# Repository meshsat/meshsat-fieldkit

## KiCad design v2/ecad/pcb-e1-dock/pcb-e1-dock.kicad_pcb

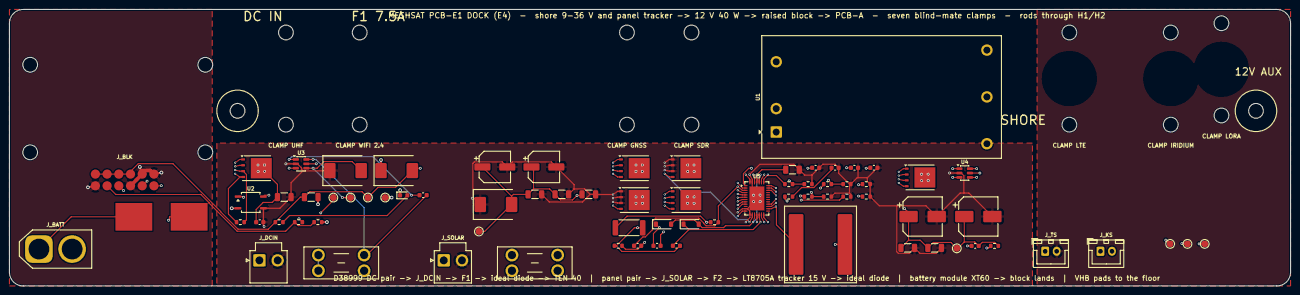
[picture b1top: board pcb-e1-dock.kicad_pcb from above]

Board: 4 copper layers, 278.0 x 60.0 mm, 97 parts (0 on the bottom side), 44 nets.

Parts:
C1, C13, C14: 10u 50V; C_1206_3216Metric
C2, C23: 100n; C_0603_1608Metric
C3: 22u 25V; C_1206_3216Metric
C4, C28: 100n 50V; C_0603_1608Metric
C11, C12: 100u 35V Panasonic EEHZK1V101XP hybrid polymer (7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; CP_Elec_6.3x7.7
C15: 4.7u 50V; C_1206_3216Metric
C16: 1n; C_0603_1608Metric
C17, C18: 470n 25V; C_0603_1608Metric
C19: 4.7u 25V; C_1206_3216Metric
C20: 1u; C_0603_1608Metric
C21: 4.7n; C_0603_1608Metric
C22: 100p; C_0603_1608Metric
C24, C25: 39u 35V Panasonic 35SVPF39M polymer (6.9 mm); CP_Elec_8x6.7
C26, C27: 10u 25V; C_1206_3216Metric
D1: SMCJ33A (input surge, datasheet 50 V 100 ms); D_SMC
D3: SMCJ15A; D_SMC
D4: SMCJ33A (panel surge); D_SMC
D5: BAT54 boost diode INTVCC -> BOOST1; D_SOD-123
D6: BAT54 boost diode INTVCC -> BOOST2; D_SOD-123
F1: 7.5 A mini blade (Keystone 3568 holder, in the cl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; Fuseholder_Blade_Mini_Keystone_3568
F2: 10 A mini blade (Keystone 3568 holder, in the cle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; Fuseholder_Blade_Mini_Keystone_3568
H1, H2: M3 rod pass-through, PCB-A standoff stands here; MountingHole_3.2mm_M3
H3, H4, H5, H6: M3 standoff, raised block; MountingHole_3.2mm_M3
H7, H8: M3, float clamp UHF; MountingHole_3.2mm_M3
H9, H10: M3, float clamp WIFI 2.4; MountingHole_3.2mm_M3
H11, H12: M3, float clamp GNSS; MountingHole_3.2mm_M3
H13, H14: M3, float clamp SDR; MountingHole_3.2mm_M3
H15, H16: M3, float clamp LTE; MountingHole_3.2mm_M3
H17, H18: M3, float clamp IRIDIUM; MountingHole_3.2mm_M3
H19, H20: M3, float clamp LORA; MountingHole_3.2mm_M3
J_BATT: battery module lead (XT60-M, 60 A): + - ; fused 4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; AMASS_XT60-M_1x02_P7.20mm_Vertical
J_BLK: solder lands for the 12 signal wires to the block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; PogoTargets_2x6
J_DCIN: shore DC in 9-36 V, lead from the D38999/20FC4PN 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; JST_VH_B2P-VH_1x02_P3.96mm_Vertical
J_KS: Kelvin sense lead from the module positive termin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; JST_XH_B2B-XH-A_1x02_P2.50mm_Vertical
J_SOLAR: bare 12 V class panel in, lead from the D38999 sp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; JST_VH_B2P-VH_1x02_P3.96mm_Vertical
J_TS: module thermistor lead (XH2.5): 103AT to the char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; JST_XH_B2B-XH-A_1x02_P2.50mm_Vertical
L1: 10uH Coilcraft XAL1510-103MED (Isat 26 A, 10.0 mm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; L_Coilcraft_XAL1510-103
LED1: green: shore 12 V present; LED_0603_1608Metric
P_CN: solder pad, 12 AWG wire to the block board return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; SolderPad_8x6
P_CP: solder pad, 12 AWG wire to the block board CELL+ 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; SolderPad_8x6
Q1, Q2: BSC039N06NS 60 V 3.9 mOhm N-FET (PG-TDSON-8: 1-3 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; TDSON-8-1
Q3: BSC028N06NS 60 V 2.8 mOhm N-FET, M1 buck top (TDS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; TDSON-8-1
Q4: BSC039N06NS 60 V N-FET, M2 buck bottom; TDSON-8-1
Q5: BSC028N06NS 60 V N-FET, M3 boost bottom; TDSON-8-1
Q6: BSC039N06NS 60 V N-FET, M4 boost top; TDSON-8-1
R1, R4, R18: 100k; R_0603_1608Metric
R2: 2.2k; R_0603_1608Metric
R3: 330R; R_0603_1608Metric
R5: 5 mOhm 1% 3 W 2512 RSENSE (RALEC LR2512-23R005F4); R_2512_6332Metric
R6, R7: 100R; R_0603_1608Metric
R8: 102k 1% (RFBIN1: panel point 17.6 V); R_0603_1608Metric
R9: 7.50k 1% (RFBIN2); R_0603_1608Metric
R10: 115k 1% (RFBOUT1: 15.1 V); R_0603_1608Metric
R11: 10.0k 1% (RFBOUT2); R_0603_1608Metric
R12: 215k 1% (RT: 202 kHz); R_0603_1608Metric
R13, R16, R17: 10k; R_0603_1608Metric
R14: 100k 1%; R_0603_1608Metric
R15: 15.0k 1% (SHDN: enable above about 9.5 V); R_0603_1608Metric
TP1: DC_IN; TestPoint_Pad_D1.5mm
TP2: DC_P; TestPoint_Pad_D1.5mm
TP3: SHORE_12V; TestPoint_Pad_D1.5mm
TP4: GND; TestPoint_Pad_D1.5mm
TP5: PV_P; TestPoint_Pad_D1.5mm
TP6: TRK_OUT; TestPoint_Pad_D1.5mm
TP7: BLK_SPARE; TestPoint_Pad_D1.5mm
TP8: CELL_P_MOD; TestPoint_Pad_D1.5mm
TP9: CELL_N_MOD; TestPoint_Pad_D1.5mm
U1: TRACO TEN 40-2412WIN: isolated 9-36 V in, 12 V 3.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; Converter_DCDC_TRACO_TEN40-110xxWIRH_THT
U2: EL817S / PC817 optocoupler: LED from PCB-A SHORE_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; SOP-4_3.8x4.1mm_P2.54mm
U3, U4: LM74700-Q1 ideal-diode controller: 1 VCAP 2 GND 3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; SOT-23-6
U5: LT8705A buck-boost controller, 38-lead QFN 5x7 (p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; WQFN-38-1EP_5x7mm_P0.5mm_EP3.15x5.15mm

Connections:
/BLK_SPARE: J_BLK.12, TP7.1
/CELL_N_MOD: J_BATT.2, P_CN.1, TP9.1
/CELL_P_MOD: J_BATT.1, P_CP.1, TP8.1
/CELL_SENSE_P: J_BLK.11, J_KS.1
/DC_F: C4.2, F1.2, Q1.1, Q1.2, Q1.3, R1.2, U3.3, U3.6
/DC_IN: F1.1, J_DCIN.1, TP1.1
/DC_N: C1.2, C2.2, C11.2, C12.2, C13.2, C14.2, C15.2, C19.2, C20.2, C21.2, C22.2, C23.2, C24.2, C25.2, C26.2, C27.2, D1.1, D4.1, J_DCIN.2, J_SOLAR.2, Q4.1, Q4.2, Q4.3, Q5.1, Q5.2, Q5.3, R9.2, R11.2, R12.2, R15.2, R16.2, R17.2, U1.2, U2.3, U3.2, U4.2, U5.11, U5.13, U5.37, U5.39
/DC_P: C1.1, C2.1, D1.2, Q1.5, Q2.5, TP2.1, U1.1, U3.4, U4.4
/LED_A: LED1.2, R2.2
/OPTO_A: R3.2, U2.1
/PV_IN: F2.1, J_SOLAR.1
/PV_P: C11.1, C12.1, C13.1, C14.1, C15.1, D4.2, F2.2, Q3.5, R8.1, R14.1, TP5.1, U5.32, U5.33, U5.34
/Q1_G: Q1.4, R1.1, U3.5
/Q2_G: Q2.4, R18.1, U4.5
/REMOTE: U1.3, U2.4
/SHORE_12V: C3.1, D3.2, J_BLK.1, J_BLK.2, J_BLK.3, J_BLK.4, R2.1, TP3.1, U1.4
/SHORE_INHIBIT: J_BLK.8, R3.1, R4.1
/TRK_BG1: Q4.4, U5.14
/TRK_BG2: Q5.4, U5.16
/TRK_BOOST1: C17.1, D5.1, U5.23
/TRK_BOOST2: C18.1, D6.1, U5.17
/TRK_CSN: C16.2, R7.2, U5.2
/TRK_CSP: C16.1, R6.2, U5.3
/TRK_FBIN: R8.2, R9.1, U5.5
/TRK_FBOUT: R10.2, R11.1, U5.6
/TRK_IMONI: R16.1, U5.38
/TRK_IMONO: R17.1, U5.7
/TRK_INTVCC: C19.1, D5.2, D6.2, U5.15, U5.35, U5.36
/TRK_LDO33: C20.1, U5.4
/TRK_LSENSE: L1.2, R5.1, R6.1
/TRK_OUT: C24.1, C25.1, C26.1, C27.1, C28.2, Q2.1, Q2.2, Q2.3, Q6.5, R10.1, R18.2, TP6.1, U4.3, U4.6, U5.29, U5.30, U5.31
/TRK_RT: R12.1, U5.12
/TRK_SHDN: R14.2, R15.1, U5.1
/TRK_SS: C23.1, U5.9
/TRK_SW1: C17.2, L1.1, Q3.1, Q3.2, Q3.3, Q4.5, U5.21
/TRK_SW2: C18.2, Q5.5, Q6.1, Q6.2, Q6.3, R5.2, R7.1, U5.19
/TRK_TG1: Q3.4, U5.22
/TRK_TG2: Q6.4, U5.18
/TRK_VC: C22.1, R13.1, U5.8
/TRK_VCC1: C21.1, R13.2
/TS_MOD: J_BLK.9, J_TS.1
/U3_VCAP: C4.1, U3.1
/U4_VCAP: C28.1, U4.1
GND: C3.2, D3.1, J_BLK.5, J_BLK.6, J_BLK.7, J_BLK.10, J_TS.2, LED1.1, R4.2, TP4.1, U1.5, U2.2

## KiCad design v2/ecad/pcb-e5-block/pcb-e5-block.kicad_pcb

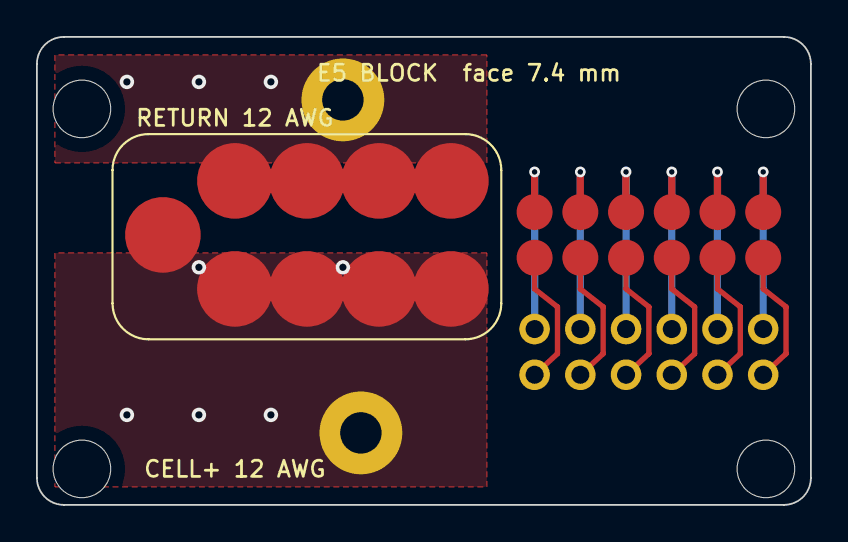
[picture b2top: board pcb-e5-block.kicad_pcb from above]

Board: 2 copper layers, 43.0 x 26.0 mm, 17 parts (0 on the bottom side), 14 nets.

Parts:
H1, H2, H3, H4: M3 standoff 6 mm to the dock strip; MountingHole_3.2mm_M3
L_SIG: plated wire lands to the strip J_BLK (net names o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; WireLands_2x6
T_CN1, T_CN2, T_CN3, T_CN4: return target (9 A pin); Mill-Max_0858_target
T_CP1, T_CP2, T_CP3, T_CP4: CELL+ target (9 A pin); Mill-Max_0858_target
T_PRE: pre-charge target (longer pin, mates first); Mill-Max_0858_target
T_SIG: signal targets (A19 J_DOCK lands here); PogoTargets_2x6
WH_CN: 12 AWG to the strip P_CN; WireHole_2mm
WH_CP: 12 AWG to the strip P_CP; WireHole_2mm

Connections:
CELL+: T_CP1.1, T_CP2.1, T_CP3.1, T_CP4.1, T_PRE.1, WH_CP.1
CELL_N: T_CN1.1, T_CN2.1, T_CN3.1, T_CN4.1, WH_CN.1
CELL_SENSE_P_P11: L_SIG.5, T_SIG.5
DOCK_SPARE_P12: L_SIG.6, T_SIG.6
GND_P5: L_SIG.11, T_SIG.11
GND_P6: L_SIG.12, T_SIG.12
GND_P7: L_SIG.1, T_SIG.1
GND_P10: L_SIG.4, T_SIG.4
SHORE_12V_P1: L_SIG.7, T_SIG.7
SHORE_12V_P2: L_SIG.8, T_SIG.8
SHORE_12V_P3: L_SIG.9, T_SIG.9
SHORE_12V_P4: L_SIG.10, T_SIG.10
SHORE_INHIBIT_P8: L_SIG.2, T_SIG.2
TS_CHG_P9: L_SIG.3, T_SIG.3

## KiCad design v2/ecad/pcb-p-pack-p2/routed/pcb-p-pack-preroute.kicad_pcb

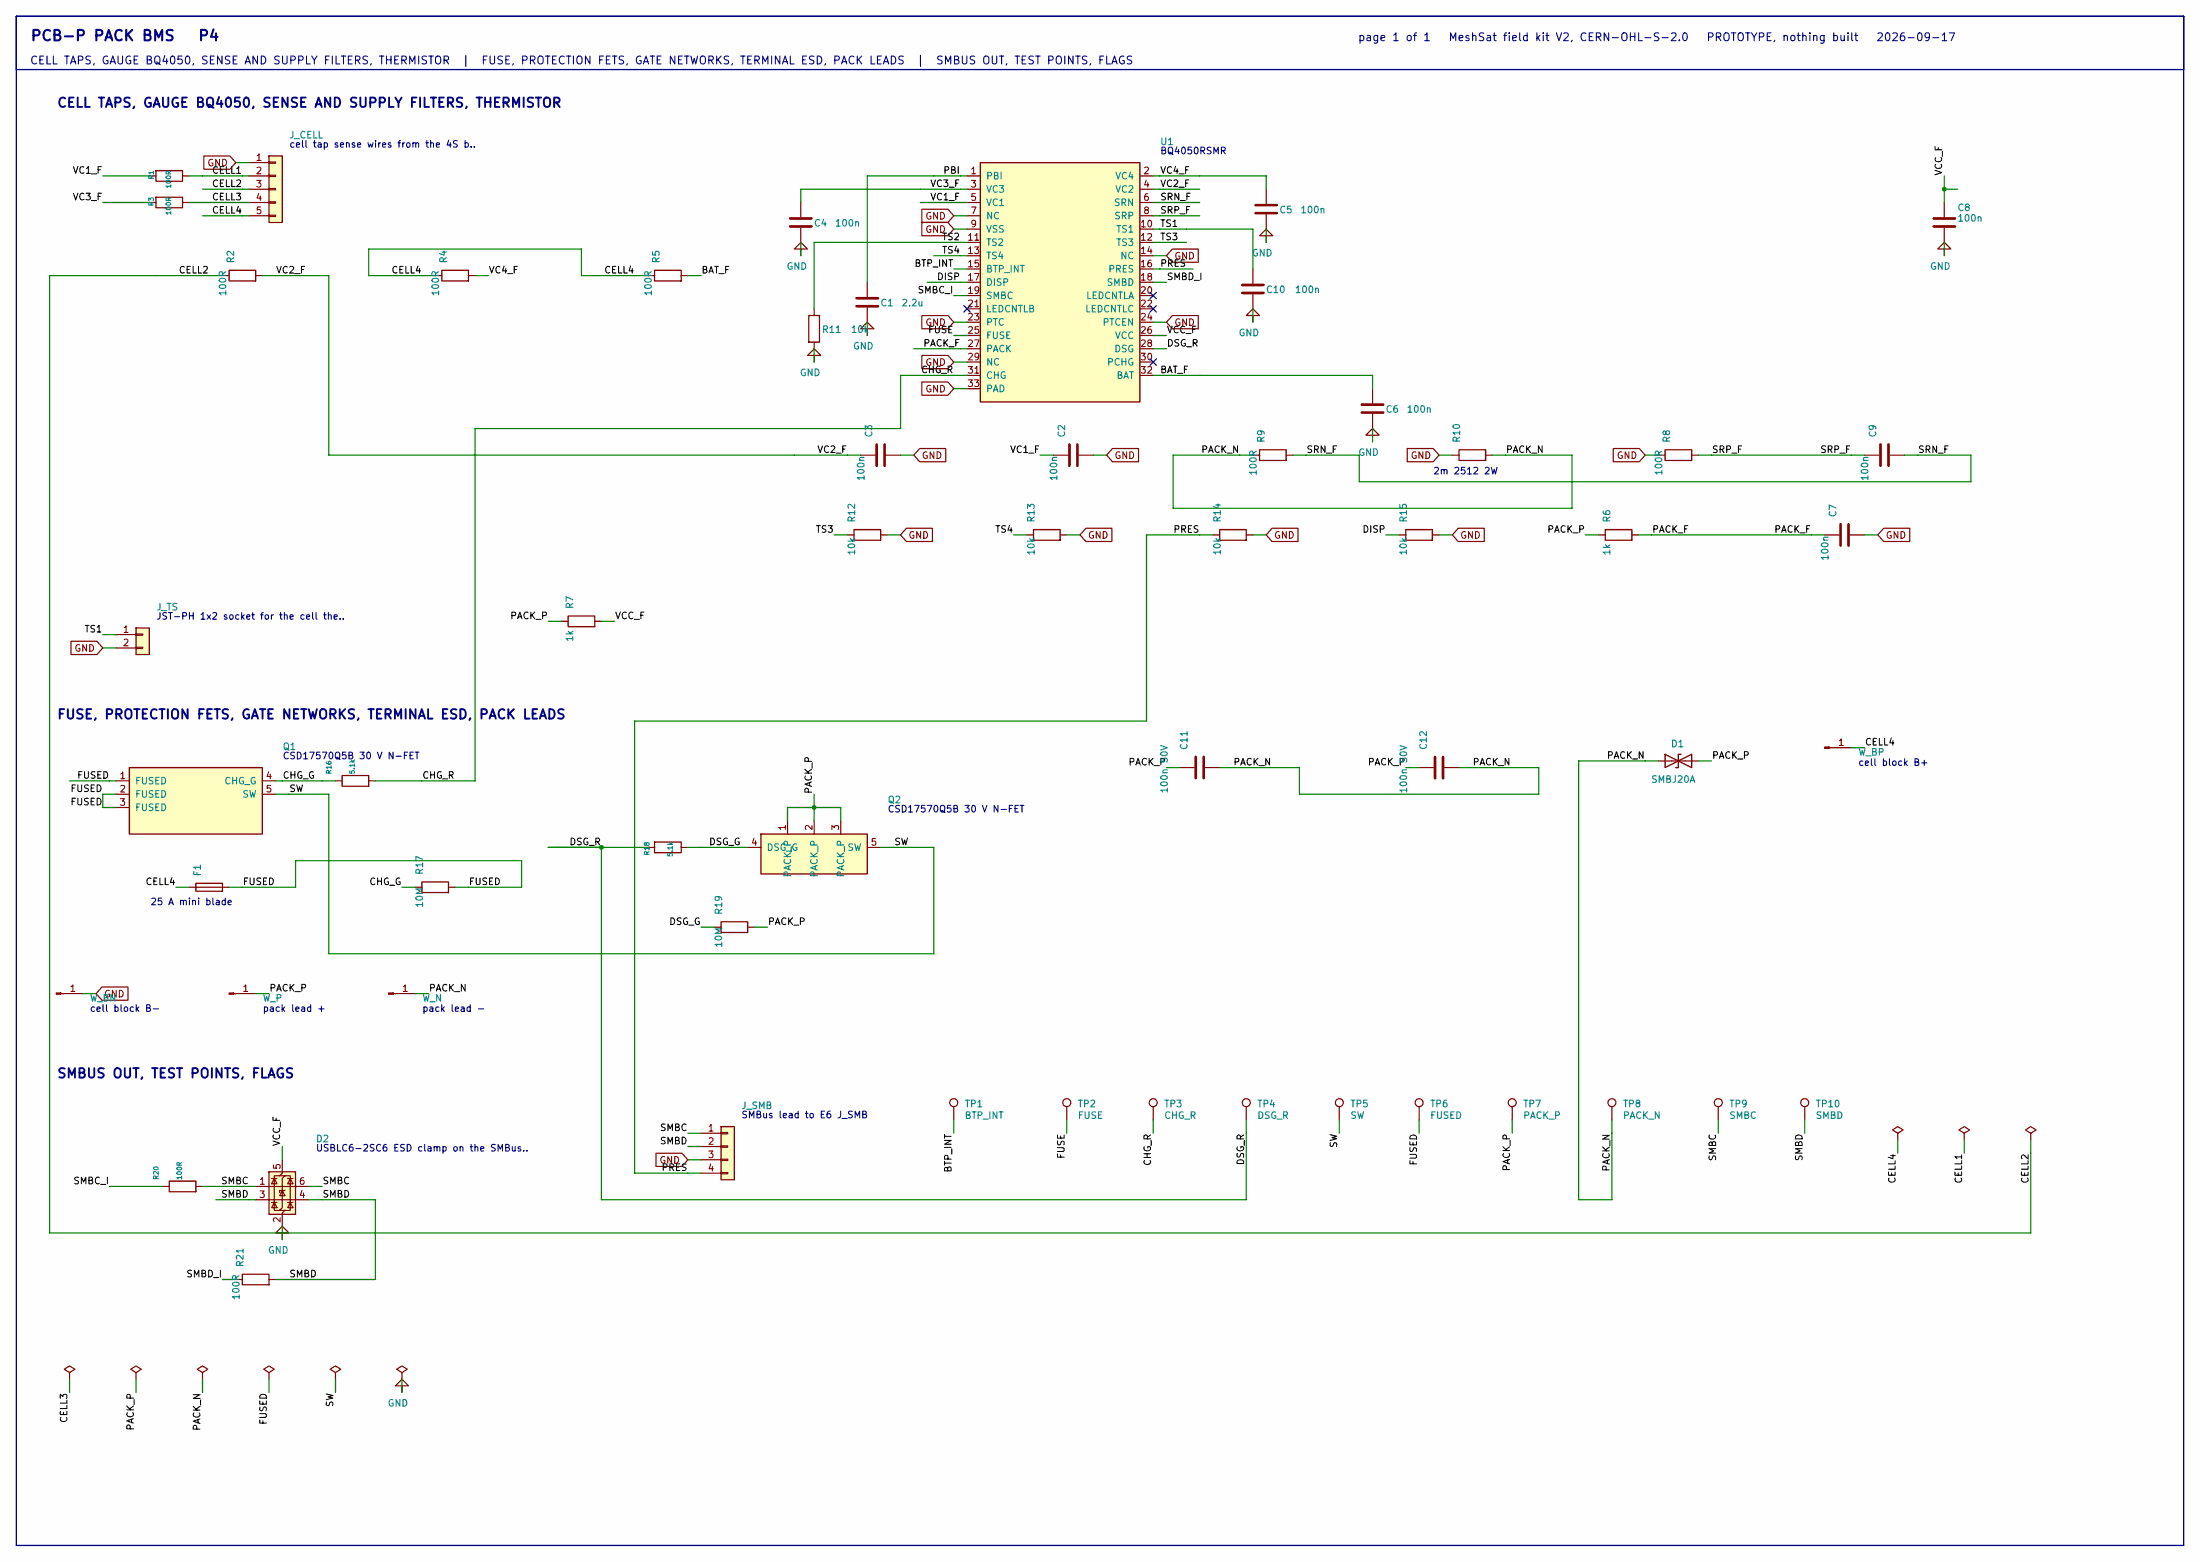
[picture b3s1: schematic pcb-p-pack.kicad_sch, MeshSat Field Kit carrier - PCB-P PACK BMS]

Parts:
C1: 2.2u; C_0805_2012Metric
C2, C3, C4, C5, C6, C7, C8, C9, C10: 100n; C_0603_1608Metric
C11: 100n 50V; C_0603_1608Metric
C12: 100n 50V; C_1206_3216Metric
D1: SMBJ20A; D_SMB
D2: USBLC6-2SC6 ESD clamp on the SMBus pair; SOT-23-6; LCSC C7519
F1: 25 A mini blade (Keystone 3568 holder): the pack'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; Fuseholder_Blade_Mini_Keystone_3568
J_CELL: cell tap sense wires from the 4S block (JST-XH 1x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; JST_XH_B5B-XH-A_1x05_P2.50mm_Vertical
J_SMB: SMBus lead to E6 J_SMB (JST-XH 1x4): SMBC SMBD GN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; JST_XH_B4B-XH-A_1x04_P2.50mm_Vertical
J_TS: JST-PH 1x2 socket for the cell thermistor lead (t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; JST_PH_B2B-PH-K_1x02_P2.00mm_Vertical; LCSC C5251182
Q1: CSD17570Q5B 30 V N-FET, charge switch; PowerPAK_SO-8_Single; LCSC C529279
Q2: CSD17570Q5B 30 V N-FET, discharge switch; PowerPAK_SO-8_Single; LCSC C529279
R1, R2, R3, R4, R5, R8, R9, R20, R21: 100R; R_0603_1608Metric
R6, R7: 1k; R_0603_1608Metric
R10: 2m 2512 2W (sense); R_2512_6332Metric
R11, R12, R13, R14, R15: 10k; R_0603_1608Metric
R16, R18: 5.1k; R_0603_1608Metric
R17, R19: 10M; R_0603_1608Metric
TP1: BTP_INT; TestPoint_Pad_D1.5mm
TP2: FUSE; TestPoint_Pad_D1.5mm
TP3: CHG_R; TestPoint_Pad_D1.5mm
TP4: DSG_R; TestPoint_Pad_D1.5mm
TP5: SW; TestPoint_Pad_D1.5mm
TP6: FUSED; TestPoint_Pad_D1.5mm
TP7: PACK_P; TestPoint_Pad_D1.5mm
TP8: PACK_N; TestPoint_Pad_D1.5mm
TP9: SMBC; TestPoint_Pad_D1.5mm
TP10: SMBD; TestPoint_Pad_D1.5mm
U1: BQ4050RSMR: SMBus 1.1 gas gauge, primary protecti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; QFN-32-1EP_5x5mm_P0.5mm_EP3.1x3.1mm; LCSC C157570
W_BN: cell block B- (12 AWG from the block's negative s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; SolderWire-2.5sqmm_1x01_D2.4mm_OD3.6mm
W_BP: cell block B+ (12 AWG from the block's positive s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; SolderWire-2.5sqmm_1x01_D2.4mm_OD3.6mm
W_N: pack lead - (12 AWG to the XT60 on E6 J_BATT pin 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; SolderWire-2.5sqmm_1x01_D2.4mm_OD3.6mm
W_P: pack lead + (12 AWG to the XT60 on E6 J_BATT pin 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; SolderWire-2.5sqmm_1x01_D2.4mm_OD3.6mm

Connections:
/BAT_F: C6.1, R5.2, U1.32 (BAT)
/BTP_INT: TP1.1, U1.15 (BTP_INT)
/CELL1: J_CELL.2, R1.1
/CELL2: J_CELL.3, R2.1
/CELL3: J_CELL.4, R3.1
/CELL4: F1.1, J_CELL.5, R4.1, R5.1, W_BP.1
/CHG_G: Q1.4 (CHG_G), R16.1, R17.1
/CHG_R: R16.2, TP3.1, U1.31 (CHG)
/DISP: R15.1, U1.17 (DISP)
/DSG_G: Q2.4 (DSG_G), R18.1, R19.1
/DSG_R: R18.2, TP4.1, U1.28 (DSG)
/FUSE: TP2.1, U1.25 (FUSE)
/FUSED: F1.2, Q1.1 (FUSED), Q1.2 (FUSED), Q1.3 (FUSED), R17.2, TP6.1
/PACK_F: C7.1, R6.2, U1.27 (PACK)
/PACK_N: C11.2, C12.2, D1.1 (A1), R9.1, R10.2, TP8.1, W_N.1
/PACK_P: C11.1, C12.1, D1.2 (A2), Q2.1 (PACK_P), Q2.2 (PACK_P), Q2.3 (PACK_P), R6.1, R7.1, R19.2, TP7.1, W_P.1
/PBI: C1.1, U1.1 (PBI)
/PRES: J_SMB.4, R14.1, U1.16 (PRES)
/SMBC: D2.1 (I/O1), D2.6 (I/O1), J_SMB.1, R20.2, TP9.1
/SMBC_I: R20.1, U1.19 (SMBC)
/SMBD: D2.3 (I/O2), D2.4 (I/O2), J_SMB.2, R21.2, TP10.1
/SMBD_I: R21.1, U1.18 (SMBD)
/SRN_F: C9.2, R9.2, U1.6 (SRN)
/SRP_F: C9.1, R8.2, U1.8 (SRP)
/SW: Q1.5 (SW), Q2.5 (SW), TP5.1
/TS1: C10.1, J_TS.1, U1.10 (TS1)
/TS2: R11.1, U1.11 (TS2)
/TS3: R12.1, U1.12 (TS3)
/TS4: R13.1, U1.13 (TS4)
/VC1_F: C2.1, R1.2, U1.5 (VC1)
/VC2_F: C3.1, R2.2, U1.4 (VC2)
/VC3_F: C4.1, R3.2, U1.3 (VC3)
/VC4_F: C5.1, R4.2, U1.2 (VC4)
/VCC_F: C8.1, D2.5 (VBUS), R7.2, U1.26 (VCC)
GND: C1.2, C2.2, C3.2, C4.2, C5.2, C6.2, C7.2, C8.2, C10.2, D2.2 (GND), J_CELL.1, J_SMB.3, J_TS.2, R8.1, R10.1, R11.2, R12.2, R13.2, R14.2, R15.2, U1.7 (NC), U1.9 (VSS), U1.14 (NC), U1.23 (PTC), U1.24 (PTCEN), U1.29 (NC), U1.33 (PAD), W_BN.1

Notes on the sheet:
PCB-P PACK BMS P4
CELL TAPS, GAUGE BQ4050, SENSE AND SUPPLY FILTERS, THERMISTOR | FUSE, PROTECTION FETS, GATE NETWORKS, TERMINAL ESD, PACK LEADS | SMBUS OUT, TEST POINTS, FLAGS
CELL TAPS, GAUGE BQ4050, SENSE AND SUPPLY FILTERS, THERMISTOR
FUSE, PROTECTION FETS, GATE NETWORKS, TERMINAL ESD, PACK LEADS
SMBUS OUT, TEST POINTS, FLAGS
page 1 of 1 MeshSat field kit V2, CERN-OHL-S-2.0 PROTOTYPE, nothing built 2026-09-17
cell tap sense wires from the 4S b..
BQ4050RSMR
2m 2512 2W
JST-PH 1x2 socket for the cell the..
CSD17570Q5B 30 V N-FET
25 A mini blade
cell block B+
cell block B-
pack lead +
pack lead -
USBLC6-2SC6 ESD clamp on the SMBus..
SMBus lead to E6 J_SMB

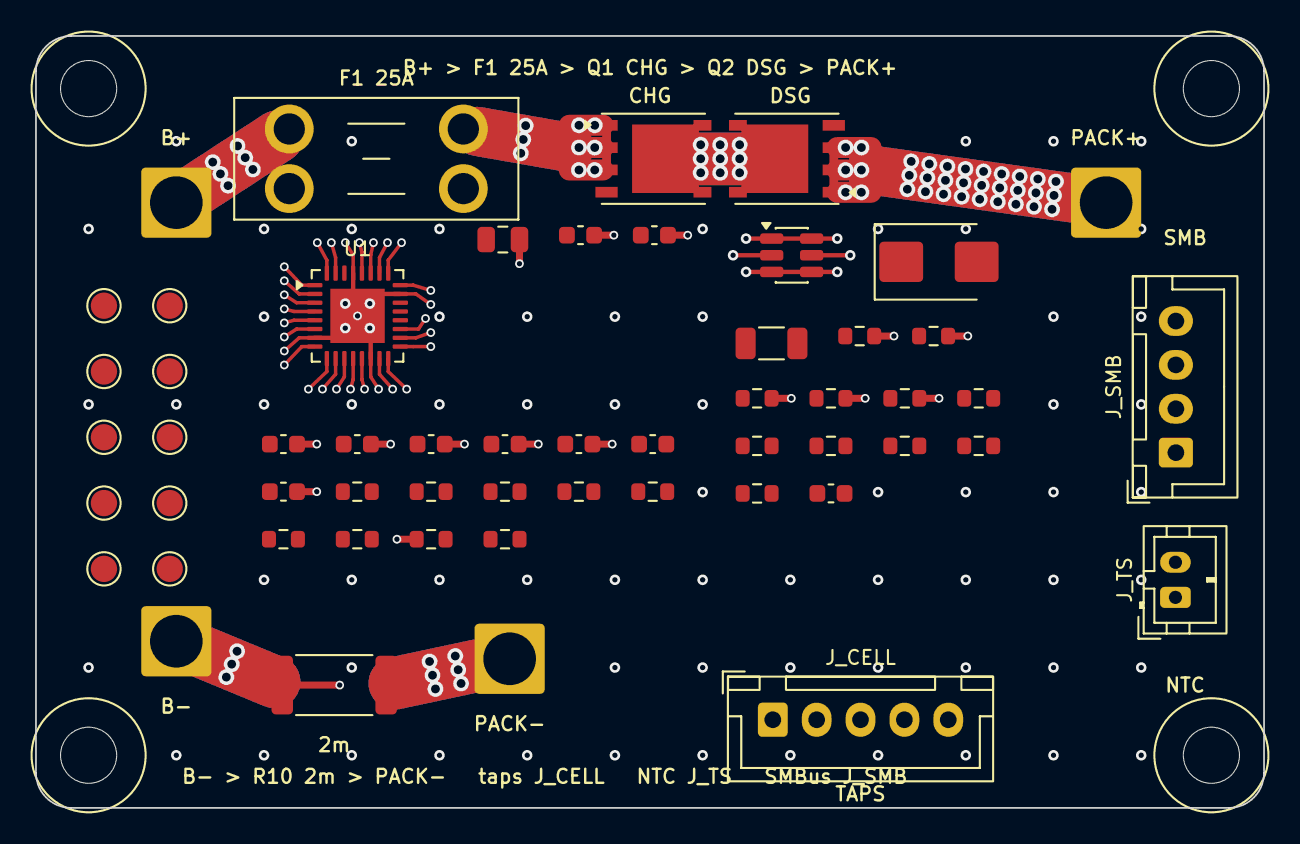
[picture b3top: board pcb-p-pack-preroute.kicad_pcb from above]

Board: 2 copper layers, 70.0 x 44.0 mm, 60 parts (0 on the bottom side), 35 nets.

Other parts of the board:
H1, H2, H3, H4: M3 into the enclosure boss; MountingHole_3.2mm_M3
